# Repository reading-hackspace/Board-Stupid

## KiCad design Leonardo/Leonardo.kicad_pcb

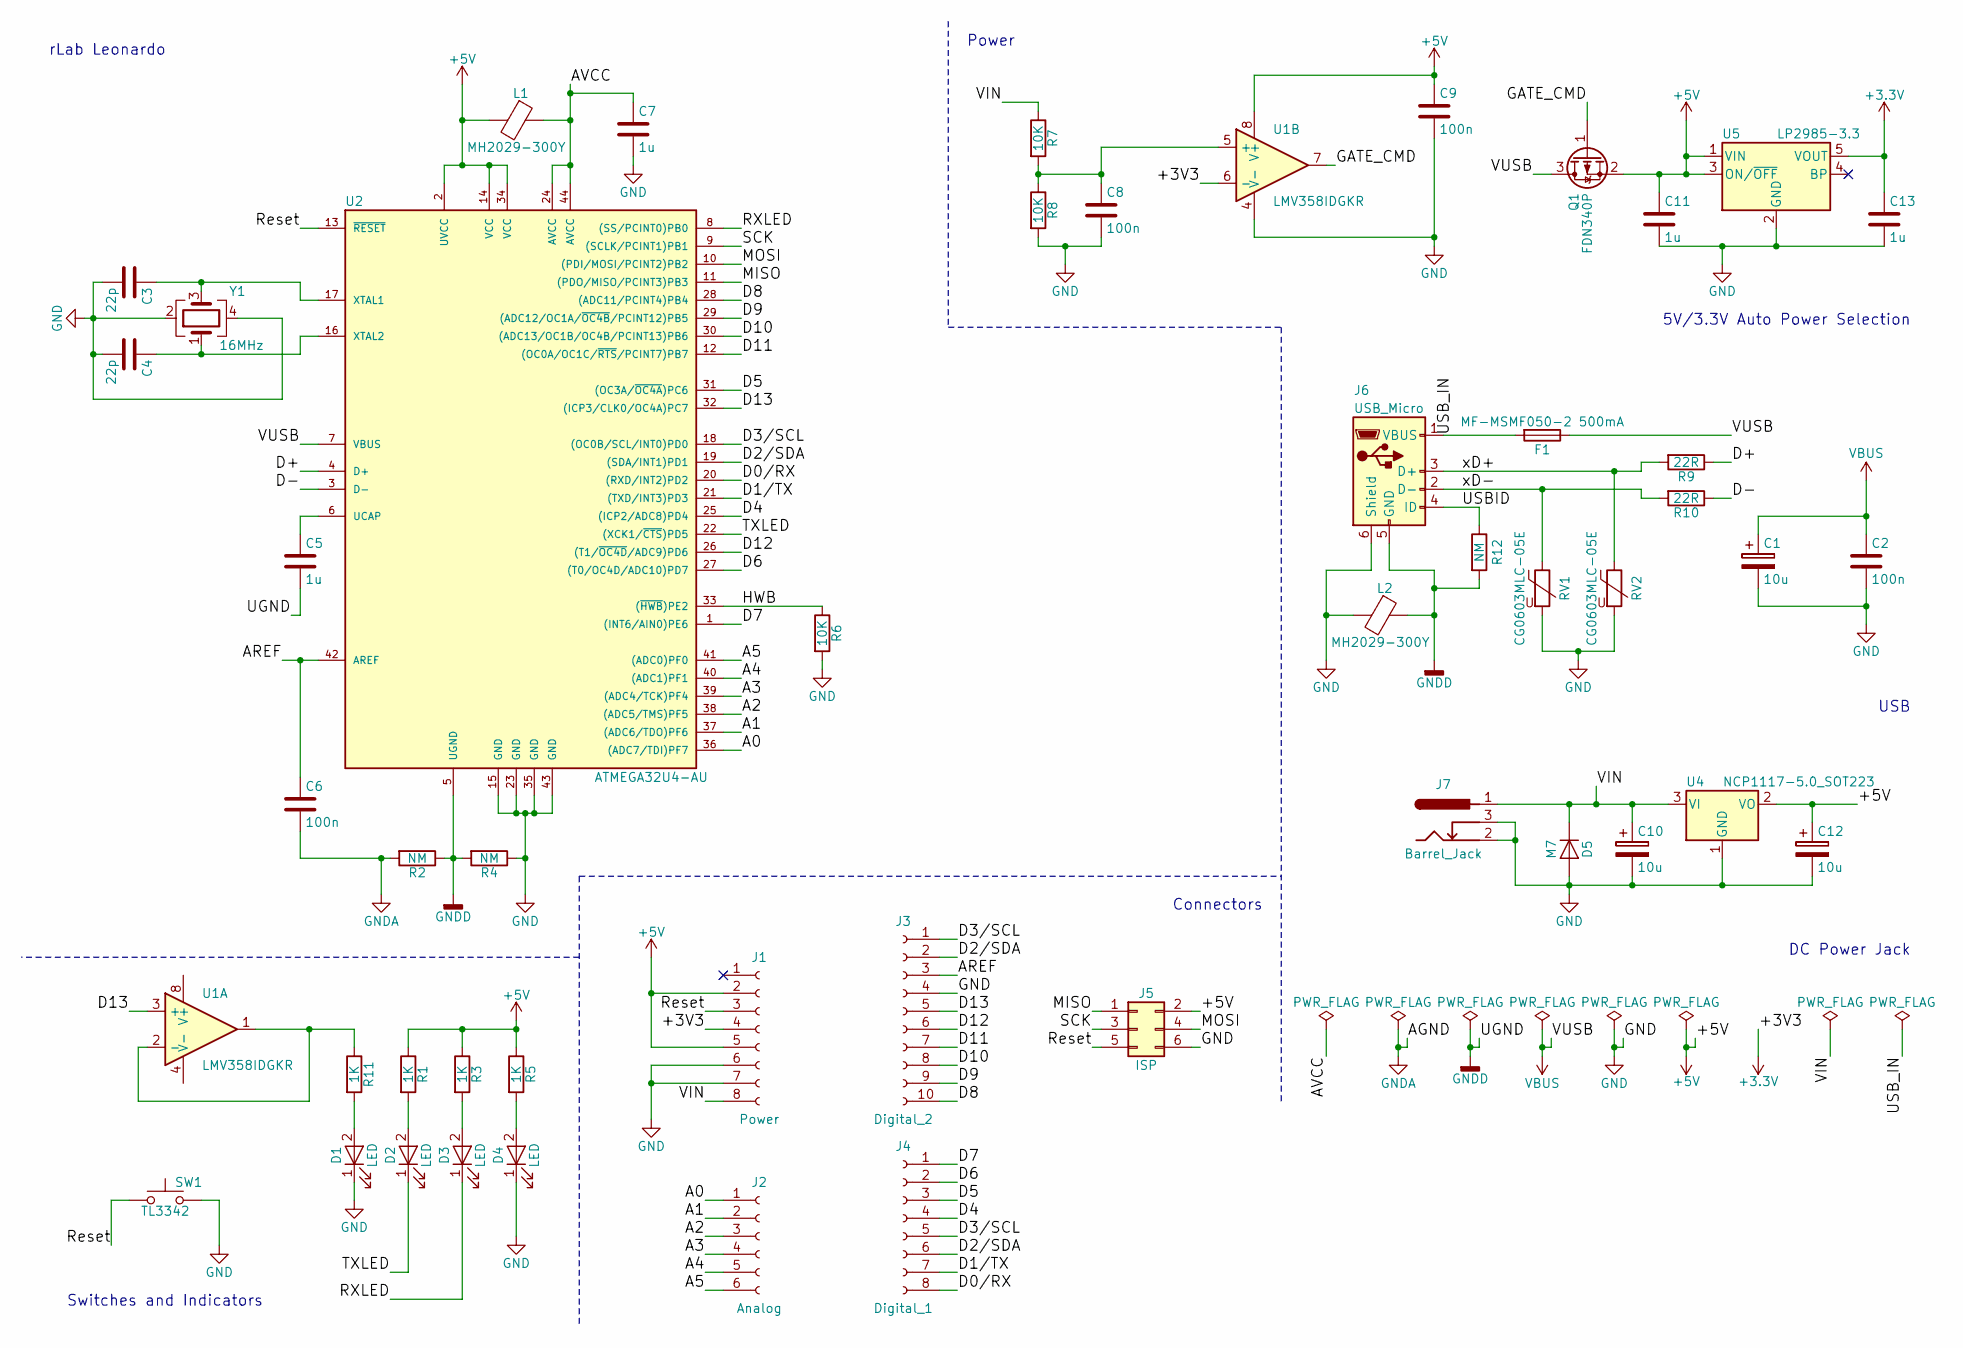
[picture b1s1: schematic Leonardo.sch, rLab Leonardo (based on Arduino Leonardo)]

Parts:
C1, C10, C12: 10u; CP_Elec_5x4.5
C2, C6, C8, C9: 100n; C_0805
C3, C4: 22p; C_0805
C5, C7, C11, C13: 1u; C_0805
D1, D2, D3, D4: LED; LED_0805
D5: M7; D_SMB
F1: MF-MSMF050-2 500mA; FUSC4632X85N
J1: Power; Socket_Strip_Straight_1x08_Pitch2.54mm
J2: Analog; Socket_Strip_Straight_1x06_Pitch2.54mm
J3: Digital_2; Socket_Strip_Straight_1x10_Pitch2.54mm
J4: Digital_1; Socket_Strip_Straight_1x08_Pitch2.54mm
J5: ISP; Pin_Header_Straight_2x03_Pitch2.54mm
J6: USB_Micro; USB_Micro-B
J7: Barrel_Jack; DC10LP socket
L1, L2: MH2029-300Y; C_0805
Q1: FDN340P; SOT-23
R1, R3, R5, R11: 1K; R_0805
R2, R4, R12: NM; R_0805
R6, R7, R8: 10K; R_0805
R9, R10: 22R; R_0805
RV1, RV2: CG0603MLC-05E; R_0603
SW1: TL3342; SW_SPST_TL3342
U1: LMV358IDGKR; TSSOP-8_3x3mm_Pitch0.65mm
U2: ATMEGA32U4-AU; LQFP-44_10x10mm_Pitch0.8mm
U4: NCP1117-5.0_SOT223; SOT-223-3Lead_TabPin2
U5: LP2985-3.3; SOT-23-5
Y1: 16MHz; Crystal_SMD_5032-4pin_5.0x3.2mm

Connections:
+3V3: C13.1, J1.4, U1.6 (-), U5.5 (VOUT)
+5V: C9.1, C11.1, C12.1, J1.2, J1.5, J5.2, L1.2, Q1.2 (S), R1.1, R3.1, R5.1, U1.8 (V+), U2.2 (UVCC), U2.14 (VCC), U2.34 (VCC), U4.2 (VO), U5.1 (VIN), U5.3 (ON/~OFF~)
/A0: J2.1, U2.36 ((ADC7/TDI)PF7)
/A1: J2.2, U2.37 ((ADC6/TDO)PF6)
/A2: J2.3, U2.38 ((ADC5/TMS)PF5)
/A3: J2.4, U2.39 ((ADC4/TCK)PF4)
/A4: J2.5, U2.40 ((ADC1)PF1)
/A5: J2.6, U2.41 ((ADC0)PF0)
/AREF: C6.1, J3.3, U2.42 (AREF)
/AVCC: C7.1, L1.1, U2.24 (AVCC), U2.44 (AVCC)
/D0/RX: J4.8, U2.20 ((RXD/INT2)PD2)
/D1/TX: J4.7, U2.21 ((TXD/INT3)PD3)
/D2/SDA: J3.2, J4.6, U2.19 ((SDA/INT1)PD1)
/D3/SCL: J3.1, J4.5, U2.18 ((OC0B/SCL/INT0)PD0)
/D4: J4.4, U2.25 ((ICP2/ADC8)PD4)
/D5: J4.3, U2.31 ((OC3A/~OC4A~)PC6)
/D6: J4.2, U2.27 ((T0/OC4D/ADC10)PD7)
/D7: J4.1, U2.1 ((INT6/AIN0)PE6)
/D8: J3.10, U2.28 ((ADC11/PCINT4)PB4)
/D9: J3.9, U2.29 ((ADC12/OC1A/~OC4B~/PCINT12)PB5)
/D10: J3.8, U2.30 ((ADC13/OC1B/OC4B/PCINT13)PB6)
/D11: J3.7, U2.12 ((OC0A/OC1C/~RTS~/PCINT7)PB7)
/D12: J3.6, U2.26 ((T1/~OC4D~/ADC9)PD6)
/D13: J3.5, U1.3 (+), U2.32 ((ICP3/CLK0/OC4A)PC7)
/D+: R9.1, U2.4 (D+)
/D-: R10.1, U2.3 (D-)
/GATE_CMD: Q1.1 (G), U1.7
/HWB: R6.1, U2.33 ((~HWB~)PE2)
/MISO: J5.1, U2.11 ((PDO/MISO/PCINT3)PB3)
/MOSI: J5.4, U2.10 ((PDI/MOSI/PCINT2)PB2)
/RXLED: D3.1 (K), U2.8 ((SS/PCINT0)PB0)
/Reset: J1.3, J5.5, SW1.1, U2.13 (~RESET~)
/SCK: J5.3, U2.9 ((SCLK/PCINT1)PB1)
/TXLED: D2.1 (K), U2.22 ((XCK1/~CTS~)PD5)
/USBID: J6.4 (ID), R12.1
/USB_IN: F1.2, J6.1 (VBUS)
/VIN: C10.1, D5.1 (K), J1.8, J7.1, R7.1, U4.3 (VI)
/xD+: J6.3 (D+), R9.2, RV2.1
/xD-: J6.2 (D-), R10.2, RV1.1
GND: C1.2, C2.2, C3.2, C4.2, C7.2, C8.2, C9.2, C10.2, C11.2, C12.2, C13.2, D1.1 (K), D4.1 (K), D5.2 (A), J1.6, J1.7, J3.4, J5.6, J6.6 (Shield), J7.2, J7.3, L2.2, R4.1, R6.2, R8.2, RV1.2, RV2.2, SW1.2, U1.4 (V-), U2.15 (GND), U2.23 (GND), U2.35 (GND), U2.43 (GND), U4.1 (GND), U5.2 (GND), Y1.2, Y1.4
GNDA: C6.2, R2.2
GNDD: C5.2, J6.5 (GND), L2.1, R2.1, R4.2, R12.2, U2.5 (UGND)
unnamed: C3.1, U2.17 (XTAL1), Y1.3
unnamed: C4.1, U2.16 (XTAL2), Y1.1
unnamed: C5.1, U2.6 (UCAP)
unnamed: C8.1, R7.2, R8.1, U1.5 (+)
unnamed: D1.2 (A), R11.2
unnamed: D2.2 (A), R1.2
unnamed: D3.2 (A), R3.2
unnamed: D4.2 (A), R5.2
unnamed: R11.1, U1.1, U1.2 (-)
VBUS: C1.1, C2.1, F1.1, Q1.3 (D), U2.7 (VBUS)

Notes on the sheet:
Switches and Indicators
Power
USB
DC Power Jack
5V/3.3V Auto Power Selection
Connectors
rLab Leonardo

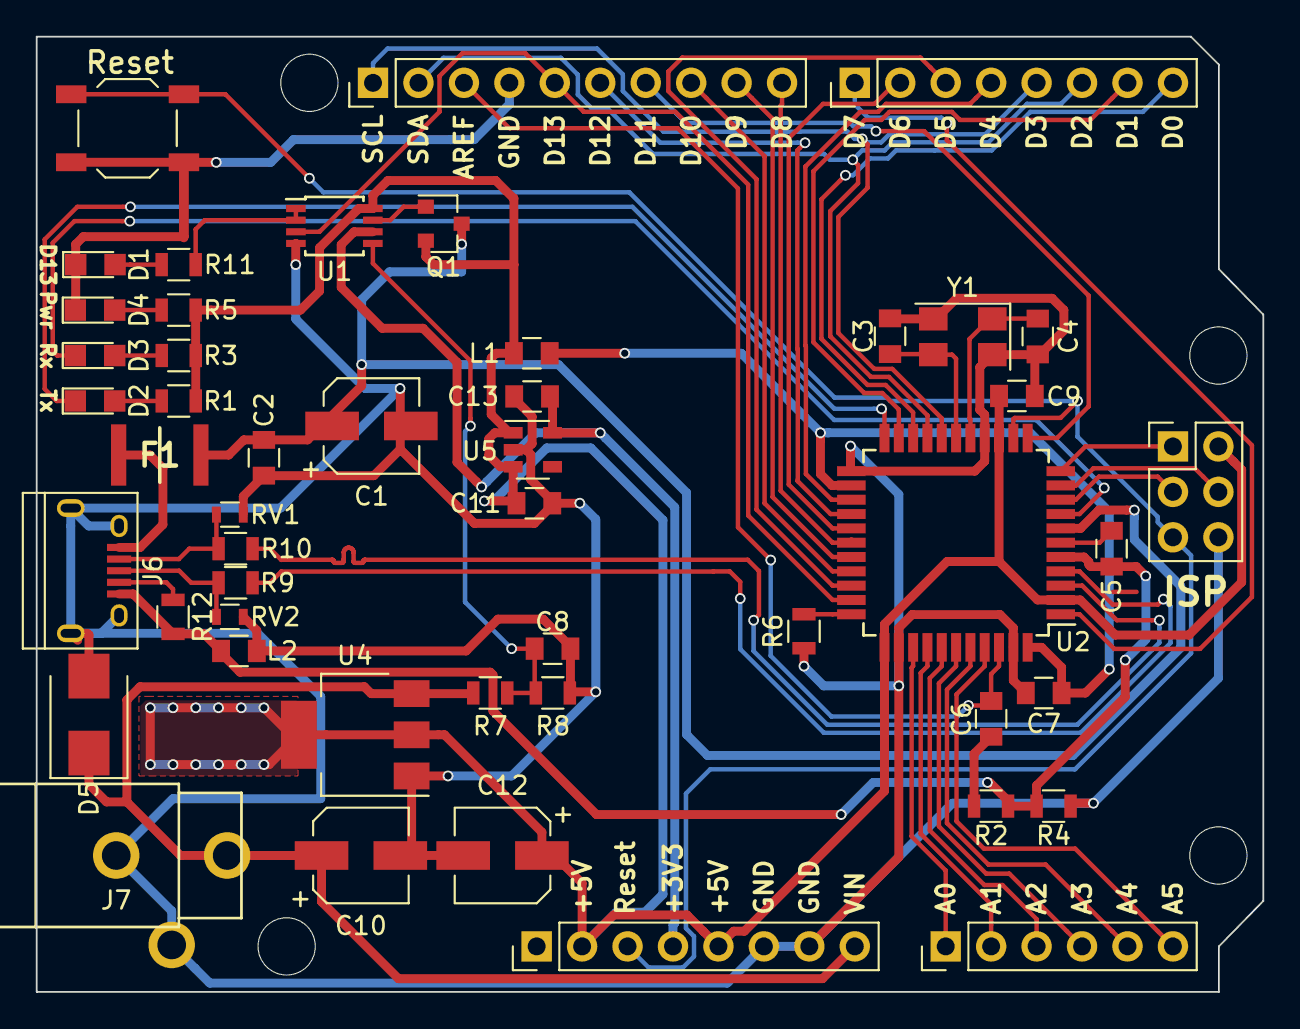
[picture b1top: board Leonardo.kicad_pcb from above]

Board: 2 copper layers, 68.5 x 53.4 mm, 49 parts (0 on the bottom side), 52 nets.

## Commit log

2017-09-16 Initial version of Leonardo Schematic in KiCAD
    For Board Stupid II
2017-09-18 Presentation shown last week
2017-09-19 Fixed missing GND
2017-09-19 Power jack - DC10LP (RS 805-1699)
2017-09-23 Filled in the component footprints
2017-09-23 Added a few missing resistors
2017-09-23 Corrected analog pins
2017-09-26 Moved DC Socket library to the Leonardo folder
2017-09-26 DXF of the Arduino outline
2017-10-03 Initial layout
2017-10-06 Tidy up a few things
2017-10-09 More tidy-up and silk screen
2017-10-09 rLab logo and info on the back
2017-10-09 Added a bit of heat dissipation for the +5V regulator
2017-10-09 More tidy up
2017-10-09 rLab logo footprint
2017-10-12 PCBWay Gerber/Drill files
2017-10-13 Fixed erroneous Rx on the front copper layer
2017-10-13 Silk screen fixes
